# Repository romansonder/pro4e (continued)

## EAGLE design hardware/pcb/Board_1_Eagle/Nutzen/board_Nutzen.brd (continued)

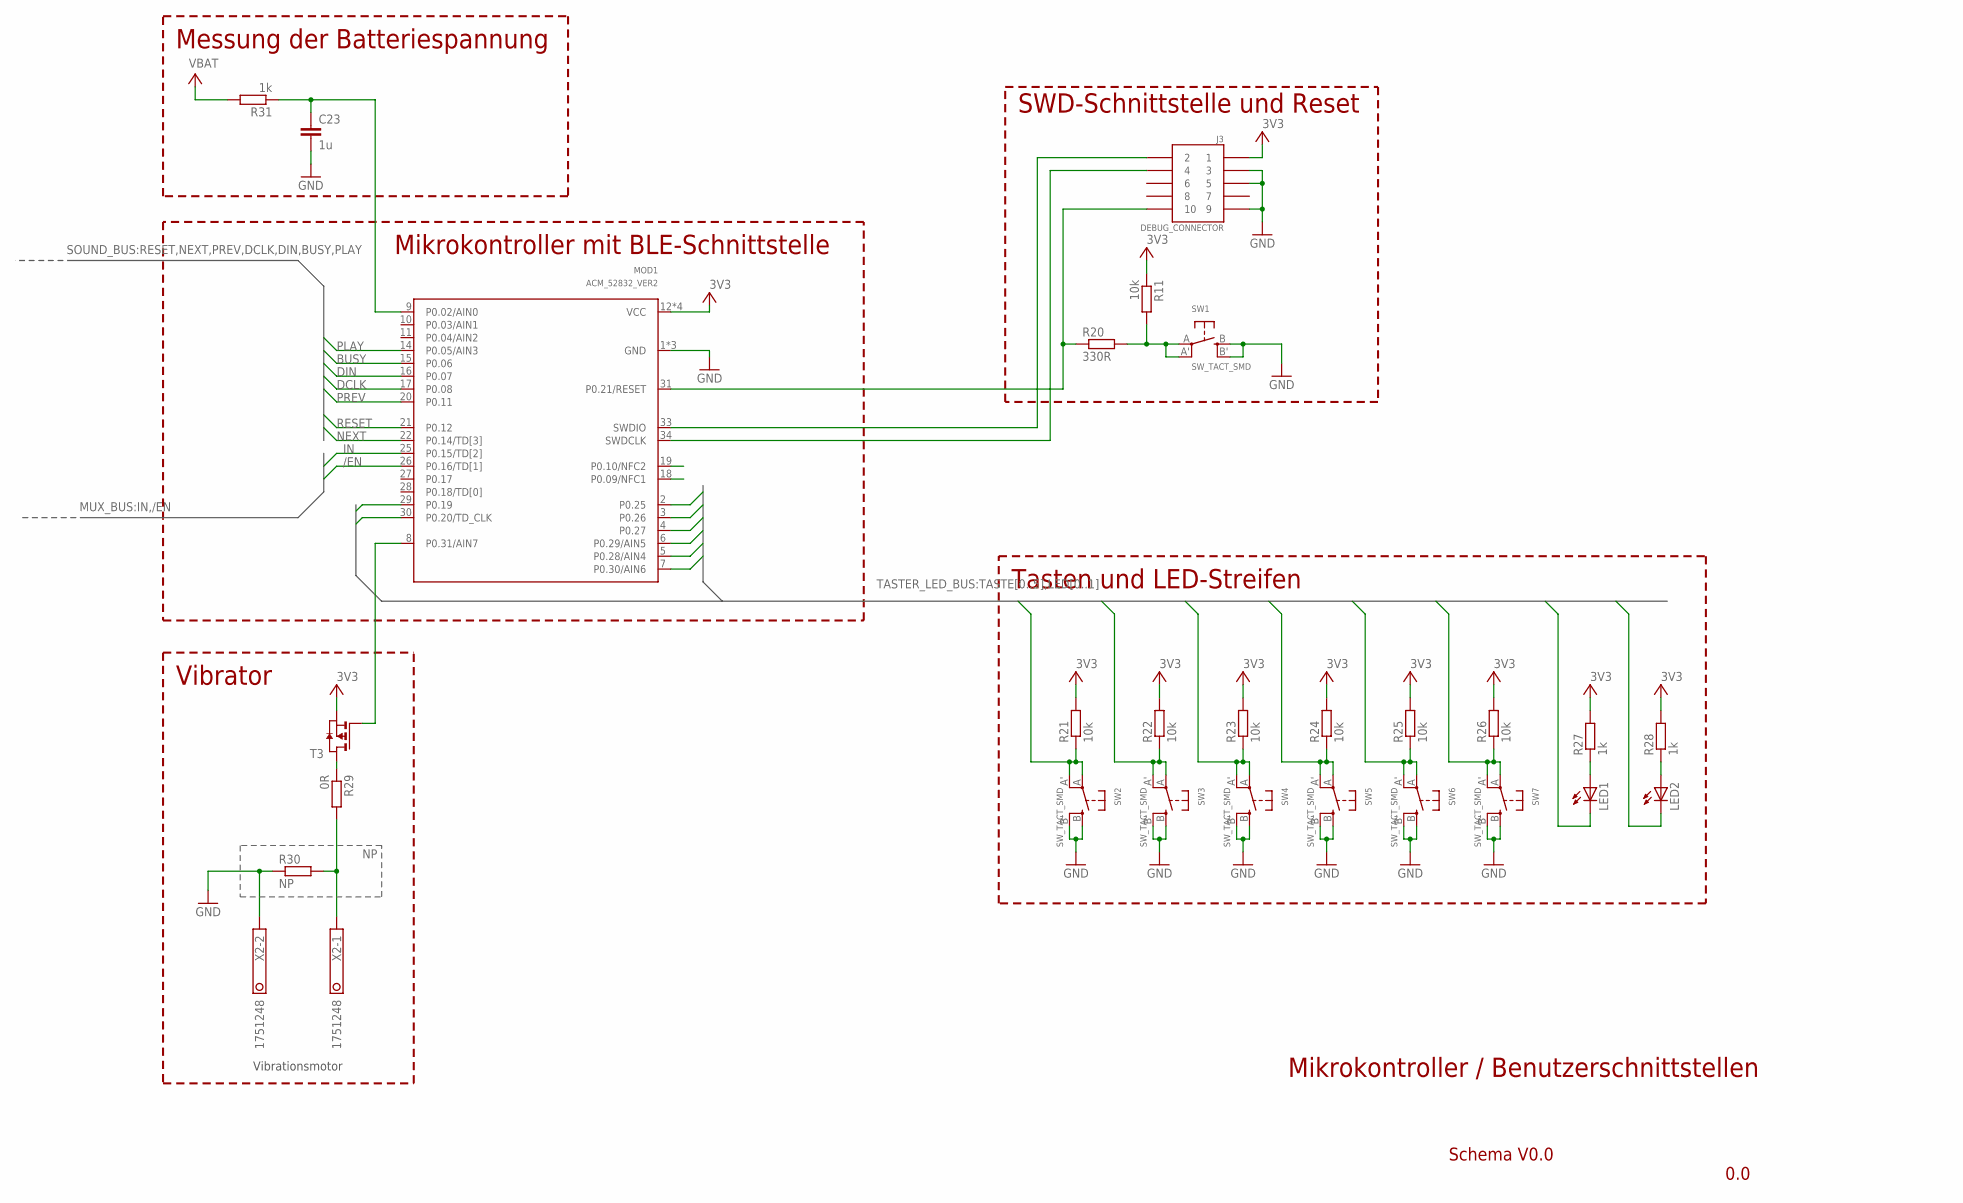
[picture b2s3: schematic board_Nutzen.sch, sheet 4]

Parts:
C23: 1u; C0603
J3: DEBUG_CONNECTOR; HDRV127P5X2-10_N
LED1, LED2: LED_E; LED_1206
MOD1: ACM_52832_VER2; ACONNO_ACM_52832
R11, R21, R22, R23, R24, R25, R26: 10k; R0603
R20: 330R; R0603
R27, R28, R31: 1k; R0603
R29: 0R; R0603
R30: NP; R0603
SW1, SW2, SW3, SW4, SW5, SW6, SW7: SW_TACT_SMD; EVQ-Q2
T3: PMOSSOT23; SOT-23
X2: 1751248

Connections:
+3V3: J3.1, MOD1.12 (VCC), MOD1.23 (VCC), MOD1.24 (VCC), MOD1.32 (VCC), R11.1, R21.2, R22.2, R23.2, R24.2, R25.2, R26.2, R27.2, R28.2, T3.2 (S); also elsewhere on the board
/EN: MOD1.26 (P0.16/TD[1]); also elsewhere on the board
BUSY: MOD1.15 (P0.06); also elsewhere on the board
DCLK: MOD1.17 (P0.08); also elsewhere on the board
DIN: MOD1.16 (P0.07); also elsewhere on the board
GND: C23.2, J3.3, J3.5, J3.9, MOD1.1 (GND), MOD1.13 (GND), MOD1.35 (GND), R30.1, SW1.B (S), SW1.B' (S1), SW2.B (S), SW2.B' (S1), SW3.B (S), SW3.B' (S1), SW4.B (S), SW4.B' (S1), SW5.B (S), SW5.B' (S1), SW6.B (S), SW6.B' (S1), SW7.B (S), SW7.B' (S1), X2.2; also elsewhere on the board
IN: MOD1.25 (P0.15/TD[2]); also elsewhere on the board
LED0: LED1.C, MOD1.29 (P0.19); also elsewhere on the board
LED1: LED2.C, MOD1.30 (P0.20/TD_CLK); also elsewhere on the board
unnamed: R11.2, R20.2, SW1.A, SW1.A' (P1)
unnamed: J3.4, MOD1.34 (SWDCLK)
unnamed: J3.10, MOD1.31 (P0.21/RESET), R20.1
unnamed: J3.2, MOD1.33 (SWDIO)
unnamed: LED1.A, R27.1
unnamed: C23.1, MOD1.9 (P0.02/AIN0), R31.1
unnamed: LED2.A, R28.1
unnamed: R29.2, R30.2, X2.1
unnamed: MOD1.8 (P0.31/AIN7), T3.3 (G)
unnamed: R29.1, T3.1 (D)
NEXT: MOD1.22 (P0.14/TD[3]); also elsewhere on the board
PLAY: MOD1.14 (P0.05/AIN3); also elsewhere on the board
PREV: MOD1.20 (P0.11); also elsewhere on the board
RESET: MOD1.21 (P0.12); also elsewhere on the board
TASTE0: MOD1.7 (P0.30/AIN6), R21.1, SW2.A, SW2.A' (P1); also elsewhere on the board
TASTE1: MOD1.5 (P0.28/AIN4), R22.1, SW3.A, SW3.A' (P1); also elsewhere on the board
TASTE2: MOD1.6 (P0.29/AIN5), R23.1, SW4.A, SW4.A' (P1); also elsewhere on the board
TASTE3: MOD1.4 (P0.27), R24.1, SW5.A, SW5.A' (P1); also elsewhere on the board
TASTE4: MOD1.3 (P0.26), R25.1, SW6.A, SW6.A' (P1); also elsewhere on the board
TASTE5: MOD1.2 (P0.25), R26.1, SW7.A, SW7.A' (P1); also elsewhere on the board
V+: R31.2; also elsewhere on the board

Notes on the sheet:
Vibrationsmotor
Tasten und LED-Streifen
SWD-Schnittstelle und Reset
Vibrator
Messung der Batteriespannung
Mikrokontroller mit BLE-Schnittstelle
Schema V0.0
0.0
Mikrokontroller / Benutzerschnittstellen

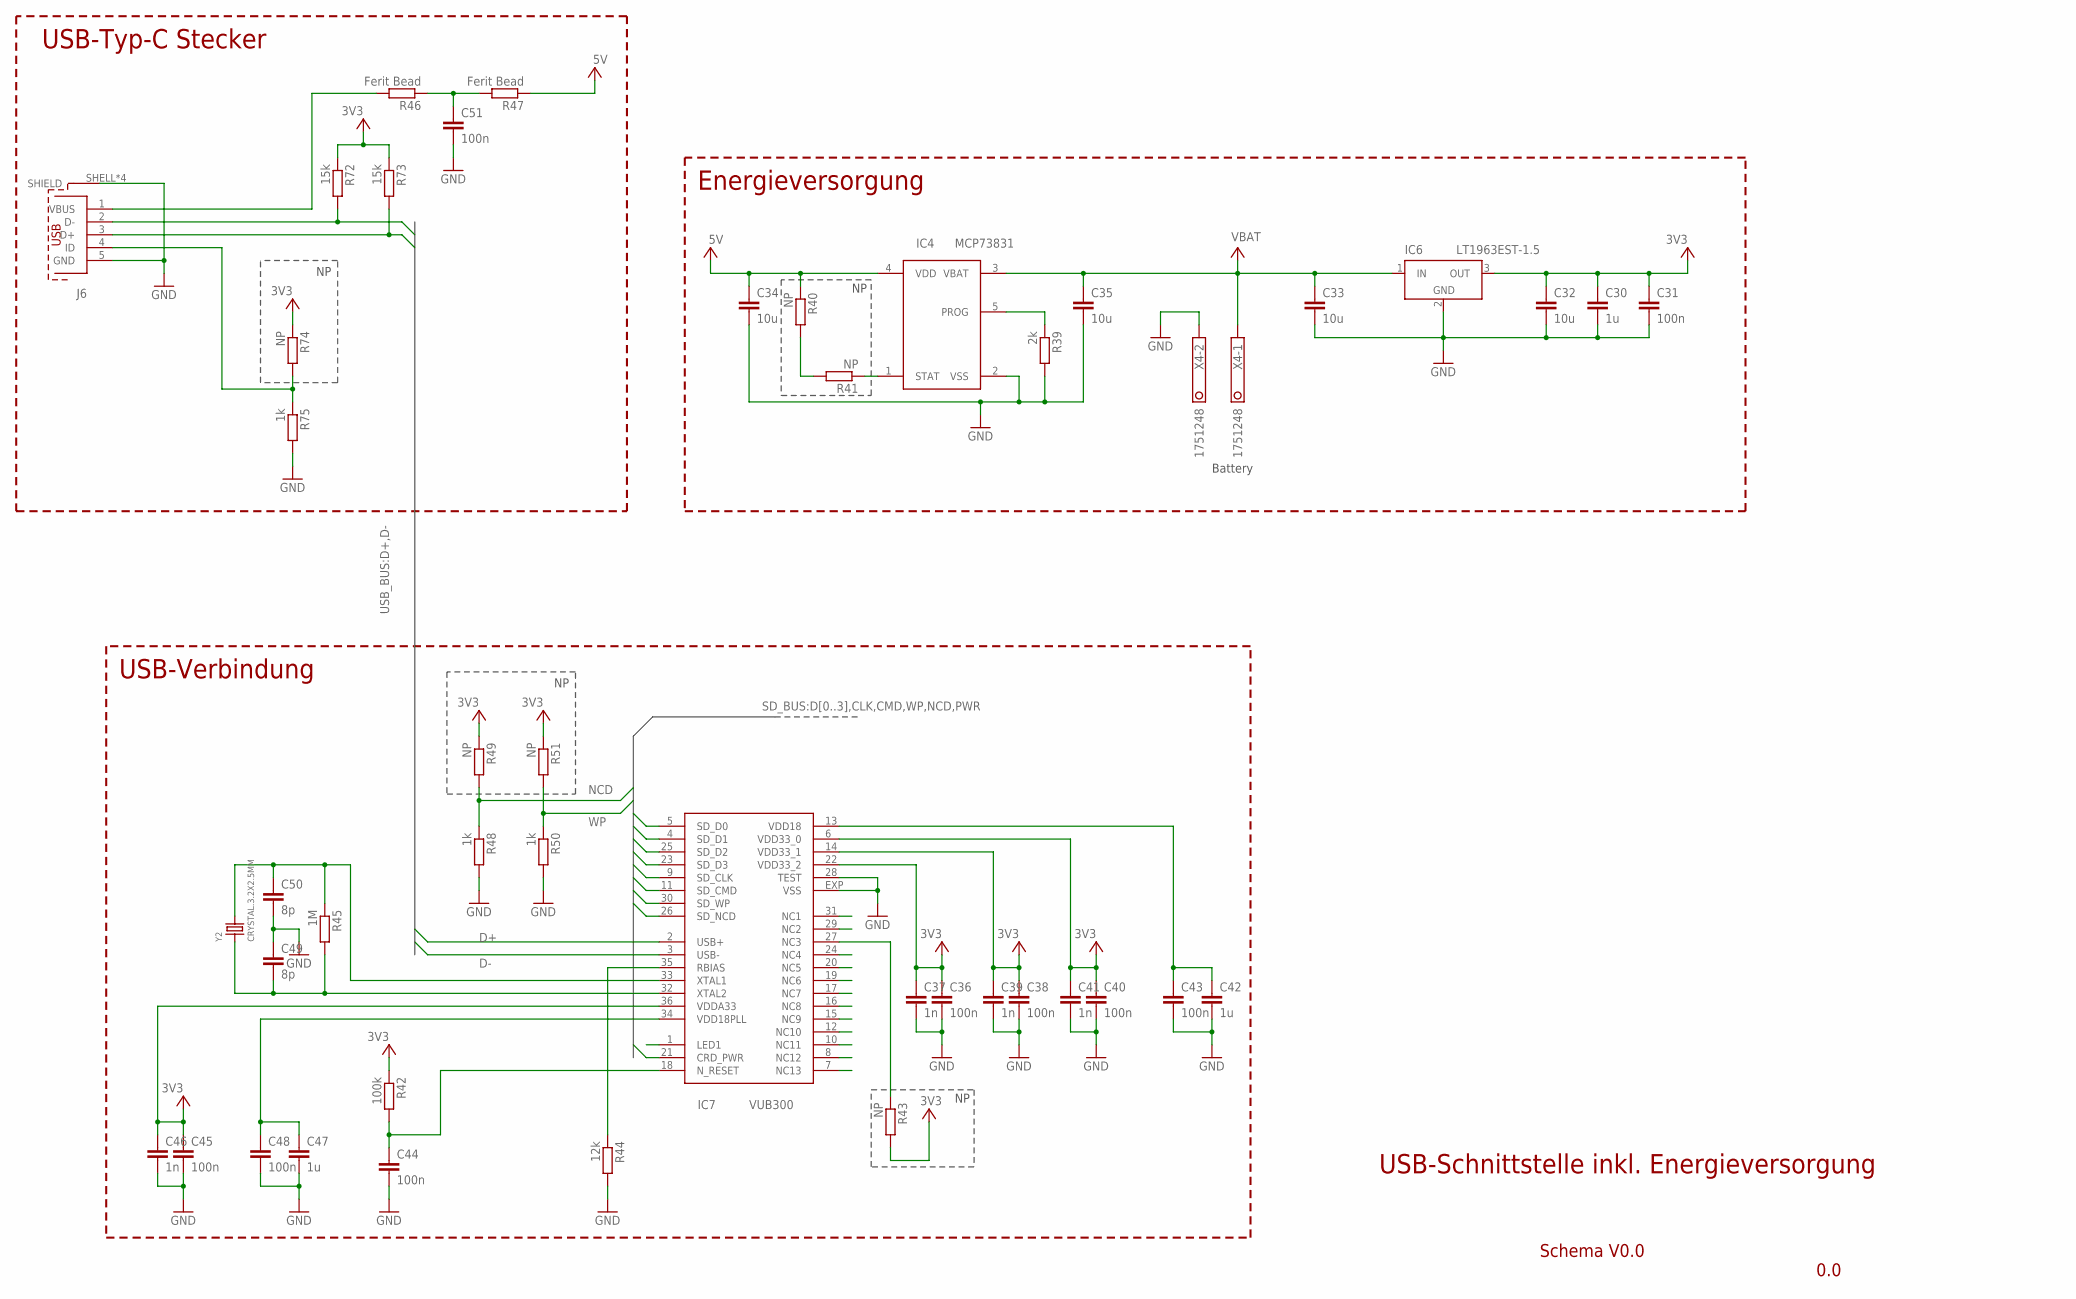
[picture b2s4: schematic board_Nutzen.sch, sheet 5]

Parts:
C30: 1u; C0603
C31, C51: 100n; C0603
C32, C33, C34, C35: 10u; C0805
C36, C38, C40, C43, C44, C45, C48: 100n; C0402
C37, C39, C41, C46: 1n; C0402
C42, C47: 1u; C0402
C49, C50: 8p; C0402
IC4: MCP73831; SOT23-5
IC6: LT1963EST-1.5; SOT223
IC7: VUB300; QFN36-6X6
J6: 629105136821
R39: 2k; R0603
R40, R41, R49, R51, R74: NP; R0603
R42: 100k; R0402
R43: NP; R0402
R44: 12k; R0402
R45: 1M; R0402
R46, R47: Ferit Bead; R0603
R48, R50, R75: 1k; R0603
R72, R73: 15k; R0402
X4: 1751248
Y2: CRYSTAL.3.2X2.5MM; 3.2X2.5MM

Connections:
+3V3: C30.1, C31.1, C32.1, C36.1, C37.1, C38.1, C39.1, C40.1, C41.1, C45.1, C46.1, IC6.3 (OUT), IC7.6 (VDD33_0), IC7.14 (VDD33_1), IC7.22 (VDD33_2), IC7.36 (VDDA33), R42.1, R43.2, R49.1, R51.1, R72.1, R73.1, R74.1; also elsewhere on the board
+5V: C34.1, IC4.4 (VDD), R40.1, R47.1; also elsewhere on the board
CLK: IC7.9 (SD_CLK); also elsewhere on the board
CMD: IC7.11 (SD_CMD); also elsewhere on the board
D0: IC7.5 (SD_D0); also elsewhere on the board
D1: IC7.4 (SD_D1); also elsewhere on the board
D2: IC7.25 (SD_D2); also elsewhere on the board
D3: IC7.23 (SD_D3); also elsewhere on the board
D+: IC7.2 (USB+), J6.3 (D+), R73.2; also elsewhere on the board
D-: IC7.3 (USB-), J6.2 (D-), R72.2; also elsewhere on the board
GND: C30.2, C31.2, C32.2, C33.2, C34.2, C35.2, C36.2, C37.2, C38.2, C39.2, C40.2, C41.2, C42.2, C43.2, C44.2, C45.2, C46.2, C47.2, C48.2, C49.1, C50.2, C51.2, IC4.2 (VSS), IC6.2 (GND), IC6.4 (GND), IC7.28 (TEST), IC7.EXP (VSS), J6.5 (GND), J6.SHELL (SHIELD), J6.SHELL1 (SHIELD), J6.SHELL2 (SHIELD), J6.SHELL3 (SHIELD), R39.2, R44.2, R48.2, R50.2, R75.2, X4.2; also elsewhere on the board
unnamed: IC4.5 (PROG), R39.1
unnamed: R40.2, R41.2
unnamed: IC4.1 (STAT), R41.1
unnamed: C44.1, IC7.18 (N_RESET), R42.2
unnamed: IC7.27 (NC3), R43.1
unnamed: IC7.35 (RBIAS), R44.1
unnamed: C49.2, IC7.32 (XTAL2), R45.2, Y2.1
unnamed: C50.1, IC7.33 (XTAL1), R45.1, Y2.3 (2)
unnamed: J6.1 (VBUS), R46.2
unnamed: C51.1, R46.1, R47.2
unnamed: J6.4 (ID), R74.2, R75.1
NCD: IC7.26 (SD_NCD), R48.1, R49.2; also elsewhere on the board
PWR: IC7.21 (CRD_PWR); also elsewhere on the board
V+: C33.1, C35.1, IC4.3 (VBAT), IC6.1 (IN), X4.1; also elsewhere on the board
VDD18: C42.1, C43.1, IC7.13 (VDD18); also elsewhere on the board
VDD18PLL: C47.1, C48.1, IC7.34 (VDD18PLL); also elsewhere on the board
WP: IC7.30 (SD_WP), R50.1, R51.2; also elsewhere on the board

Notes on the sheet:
Battery
USB-Typ-C Stecker
Energieversorgung
USB-Verbindung
Schema V0.0
0.0
USB-Schnittstelle inkl. Energieversorgung

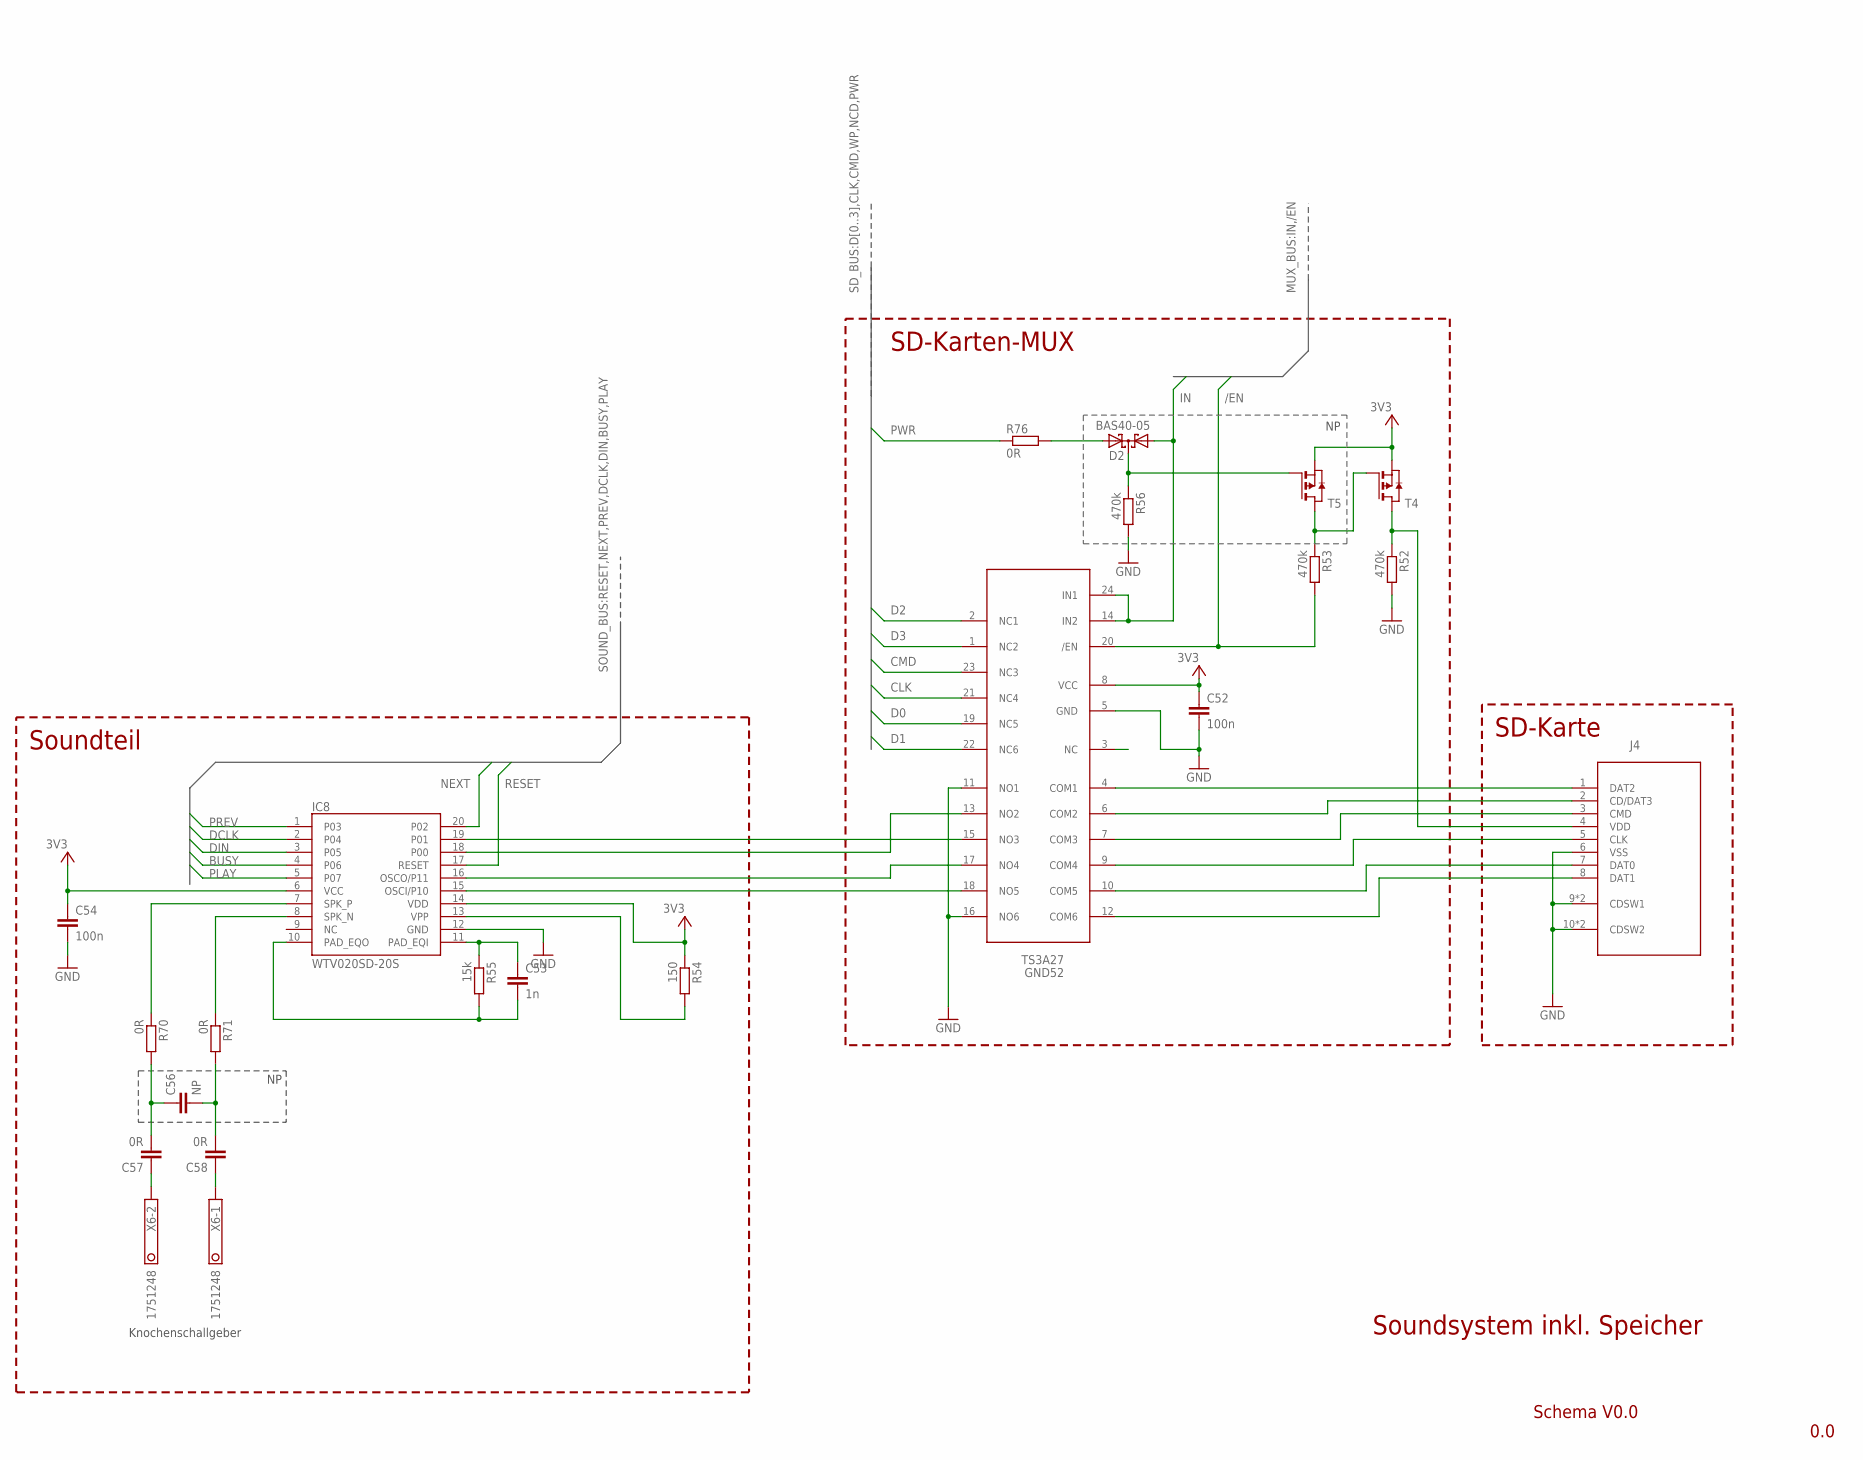
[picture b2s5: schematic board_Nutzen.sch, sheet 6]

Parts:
C52, C54: 100n; C0603
C53: 1n; C0603
C56: NP; C0603
C57, C58: 0R; C0603
D2: BAS40-05; SOT23
GND52: TS3A27; TSSOP24
IC8: WTV020SD-20S; SSOP_20
J4: 693071010811
R52, R53, R56: 470k; R0603
R54: 150; R0603
R55: 15k; R0603
R70, R71: 0R; R0603
R76: 0R; MINI_MELF-0102W
T4, T5: PMOSSOT23; SOT-23
X6: 1751248

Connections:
+3V3: C52.1, C54.1, GND52.8 (VCC), IC8.6 (VCC), IC8.14 (VDD), R54.1, T4.2 (S), T5.2 (S); also elsewhere on the board
/EN: GND52.20 (/EN), R53.2; also elsewhere on the board
BUSY: IC8.4 (P06); also elsewhere on the board
CLK: GND52.21 (NC4); also elsewhere on the board
CMD: GND52.23 (NC3); also elsewhere on the board
D0: GND52.19 (NC5); also elsewhere on the board
D1: GND52.22 (NC6); also elsewhere on the board
D2: GND52.2 (NC1); also elsewhere on the board
D3: GND52.1 (NC2); also elsewhere on the board
DCLK: IC8.2 (P04); also elsewhere on the board
DIN: IC8.3 (P05); also elsewhere on the board
GND: C52.2, C54.2, GND52.5 (GND), GND52.11 (NO1), GND52.16 (NO6), IC8.12 (GND), J4.6 (VSS), J4.9 (CDSW1), J4.9-1 (CDSW1), J4.10 (CDSW2), J4.10-1 (CDSW2), R52.2, R56.2; also elsewhere on the board
IN: D2.1 (A1), GND52.14 (IN2), GND52.24 (IN1); also elsewhere on the board
unnamed: GND52.9 (COM4), J4.5 (CLK)
unnamed: IC8.13 (VPP), R54.2
unnamed: C53.1, IC8.11 (PAD_EQI), R55.1
unnamed: GND52.17 (NO4), IC8.16 (OSCO/P11)
unnamed: GND52.18 (NO5), IC8.15 (OSCI/P10)
unnamed: GND52.6 (COM2), J4.2 (CD/DAT3)
unnamed: GND52.4 (COM1), J4.1 (DAT2)
unnamed: GND52.12 (COM6), J4.8 (DAT1)
unnamed: R53.1, T4.3 (G), T5.1 (D)
unnamed: D2.3 (C), R56.1, T5.3 (G)
unnamed: C57.1, X6.2
unnamed: C58.1, X6.1
unnamed: C56.2, C58.2, R71.2
unnamed: C56.1, C57.2, R70.2
unnamed: D2.2 (A2), R76.2
unnamed: GND52.15 (NO3), IC8.19 (P01)
NCD2: J4.4 (VDD), R52.1, T4.1 (D)
NEXT: IC8.20 (P02); also elsewhere on the board
PLAY: IC8.5 (P07); also elsewhere on the board
PREV: IC8.1 (P03); also elsewhere on the board
PWM1: C53.2, IC8.10 (PAD_EQO), R55.2
PWR: R76.1; also elsewhere on the board
RESET: IC8.17 (RESET); also elsewhere on the board
SDCS1: GND52.13 (NO2), IC8.18 (P00)
SDDI1: GND52.7 (COM3), J4.3 (CMD)
SDDO1: GND52.10 (COM5), J4.7 (DAT0)
SPK+1: IC8.7 (SPK_P), R70.1
SPK-1: IC8.8 (SPK_N), R71.1

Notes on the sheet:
SD-Karten-MUX
SD-Karte
Soundteil
Schema V0.0
0.0
Soundsystem inkl. Speicher
Knochenschallgeber

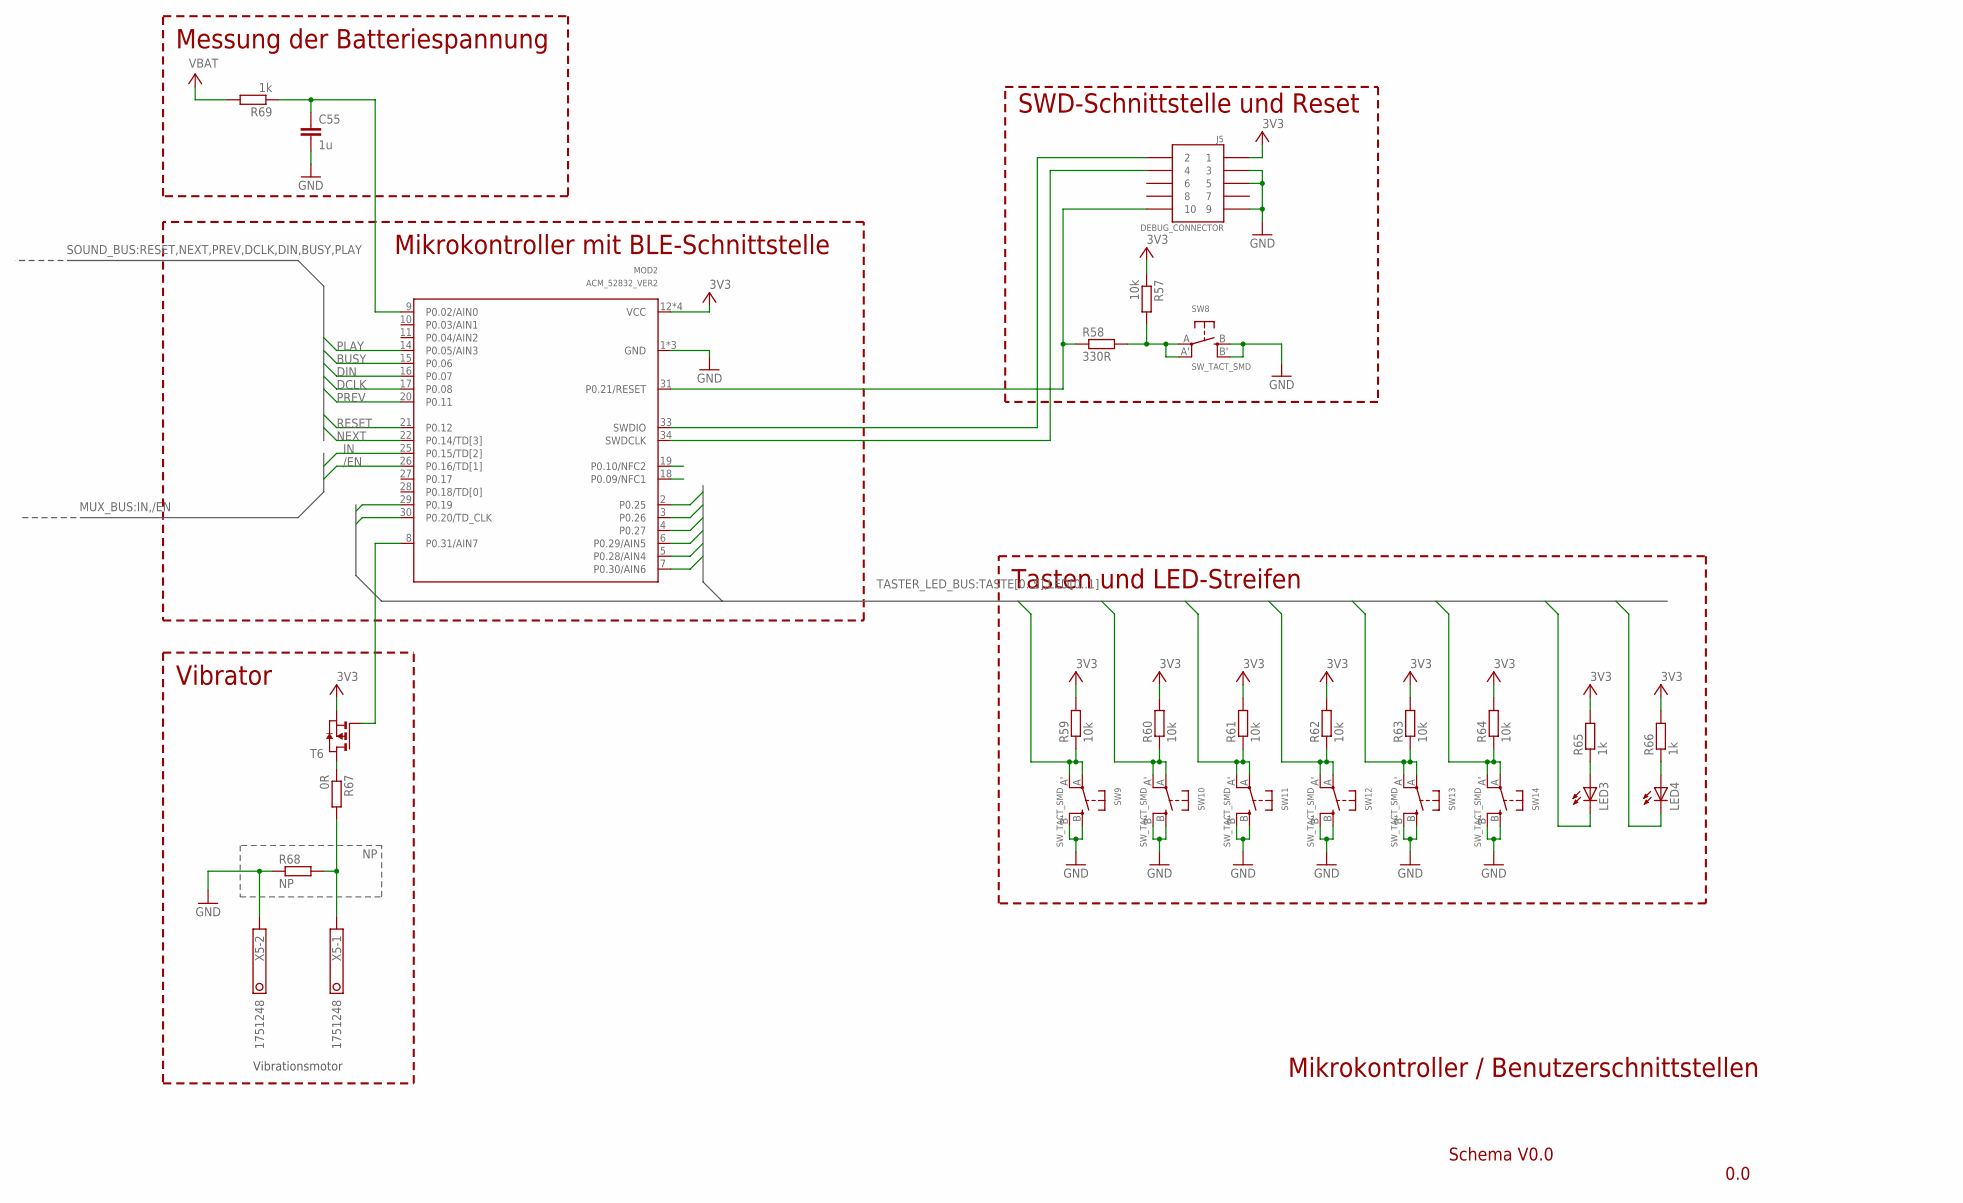
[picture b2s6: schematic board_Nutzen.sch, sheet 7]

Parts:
C55: 1u; C0603
J5: DEBUG_CONNECTOR; HDRV127P5X2-10_N
LED3, LED4: LED_E; LED_1206
MOD2: ACM_52832_VER2; ACONNO_ACM_52832
R57, R59, R60, R61, R62, R63, R64: 10k; R0603
R58: 330R; R0603
R65, R66, R69: 1k; R0603
R67: 0R; R0603
R68: NP; R0603
SW8, SW9, SW10, SW11, SW12, SW13, SW14: SW_TACT_SMD; EVQ-Q2
T6: PMOSSOT23; SOT-23
X5: 1751248

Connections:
+3V3: J5.1, MOD2.12 (VCC), MOD2.23 (VCC), MOD2.24 (VCC), MOD2.32 (VCC), R57.1, R59.2, R60.2, R61.2, R62.2, R63.2, R64.2, R65.2, R66.2, T6.2 (S); also elsewhere on the board
/EN: MOD2.26 (P0.16/TD[1]); also elsewhere on the board
BUSY: MOD2.15 (P0.06); also elsewhere on the board
DCLK: MOD2.17 (P0.08); also elsewhere on the board
DIN: MOD2.16 (P0.07); also elsewhere on the board
GND: C55.2, J5.3, J5.5, J5.9, MOD2.1 (GND), MOD2.13 (GND), MOD2.35 (GND), R68.1, SW8.B (S), SW8.B' (S1), SW9.B (S), SW9.B' (S1), SW10.B (S), SW10.B' (S1), SW11.B (S), SW11.B' (S1), SW12.B (S), SW12.B' (S1), SW13.B (S), SW13.B' (S1), SW14.B (S), SW14.B' (S1), X5.2; also elsewhere on the board
IN: MOD2.25 (P0.15/TD[2]); also elsewhere on the board
LED0: LED3.C, MOD2.29 (P0.19); also elsewhere on the board
LED1: LED4.C, MOD2.30 (P0.20/TD_CLK); also elsewhere on the board
unnamed: R57.2, R58.2, SW8.A, SW8.A' (P1)
unnamed: J5.10, MOD2.31 (P0.21/RESET), R58.1
unnamed: J5.2, MOD2.33 (SWDIO)
unnamed: J5.4, MOD2.34 (SWDCLK)
unnamed: LED3.A, R65.1
unnamed: LED4.A, R66.1
unnamed: MOD2.8 (P0.31/AIN7), T6.3 (G)
unnamed: R67.2, R68.2, X5.1
unnamed: R67.1, T6.1 (D)
unnamed: C55.1, MOD2.9 (P0.02/AIN0), R69.1
NEXT: MOD2.22 (P0.14/TD[3]); also elsewhere on the board
PLAY: MOD2.14 (P0.05/AIN3); also elsewhere on the board
PREV: MOD2.20 (P0.11); also elsewhere on the board
RESET: MOD2.21 (P0.12); also elsewhere on the board
TASTE0: MOD2.7 (P0.30/AIN6), R59.1, SW9.A, SW9.A' (P1); also elsewhere on the board
TASTE1: MOD2.5 (P0.28/AIN4), R60.1, SW10.A, SW10.A' (P1); also elsewhere on the board
TASTE2: MOD2.6 (P0.29/AIN5), R61.1, SW11.A, SW11.A' (P1); also elsewhere on the board
TASTE3: MOD2.4 (P0.27), R62.1, SW12.A, SW12.A' (P1); also elsewhere on the board
TASTE4: MOD2.3 (P0.26), R63.1, SW13.A, SW13.A' (P1); also elsewhere on the board
TASTE5: MOD2.2 (P0.25), R64.1, SW14.A, SW14.A' (P1); also elsewhere on the board
V+: R69.2; also elsewhere on the board

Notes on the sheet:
Vibrationsmotor
Tasten und LED-Streifen
SWD-Schnittstelle und Reset
Vibrator
Messung der Batteriespannung
Mikrokontroller mit BLE-Schnittstelle
Schema V0.0
0.0
Mikrokontroller / Benutzerschnittstellen

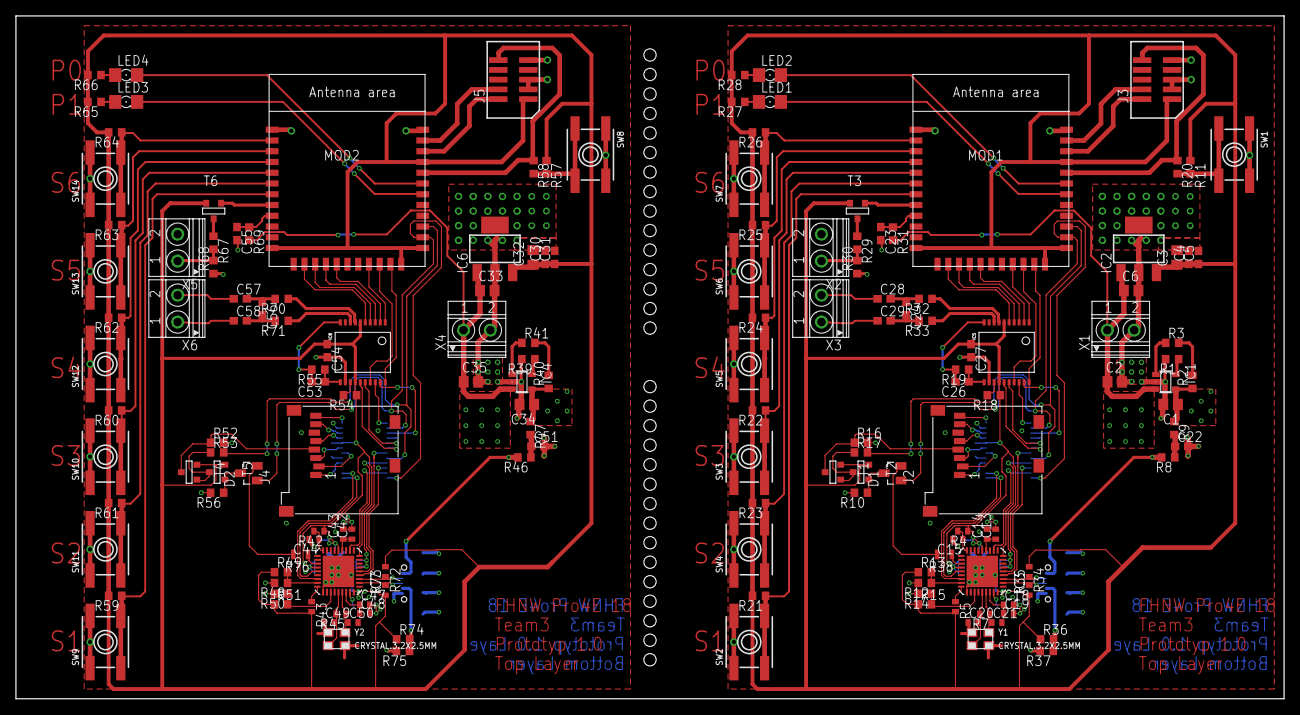
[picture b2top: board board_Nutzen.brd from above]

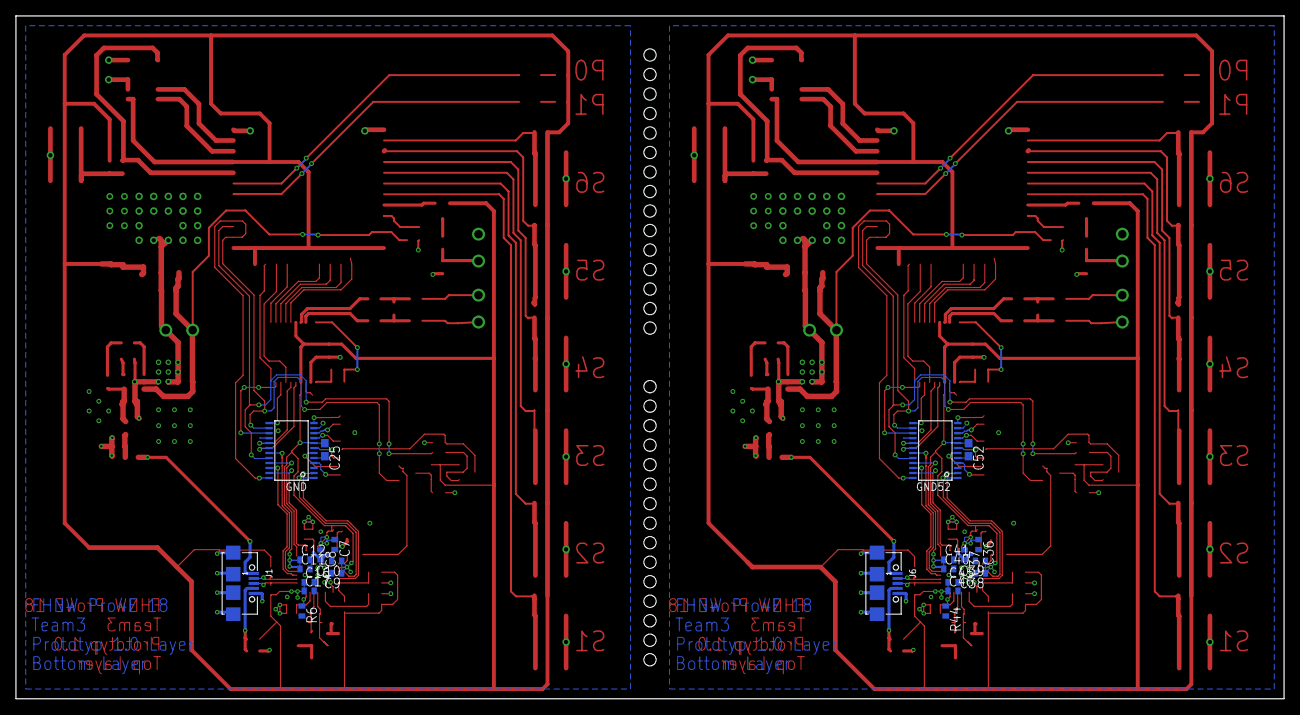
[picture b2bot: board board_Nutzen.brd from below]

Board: 2 copper layers, 165.1 x 88.9 mm, 186 parts (24 on the bottom side), 122 nets.

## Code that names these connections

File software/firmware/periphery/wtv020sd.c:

/* lizenz */

/* wtv020sd Audiointerface */

#include <stdbool.h>
#include <stdint.h>

#include "nrf_delay.h"
#include "nrf_gpio.h"
#include "dojo.h"


#include "wtv020sd.h"

/******************************************************************************/
static void wtv020sd_send(uint16_t command);

/******************************************************************************/
/* edit IO-Ports as you need them */
static const uint32_t data_pin = AUDIO_DIN_PIN;
static const uint32_t reset_pin = AUDIO_RESET_PIN;
static const uint32_t clk_pin = AUDIO_DCLK_PIN;
static const uint32_t busy_pin = AUDIO_BUSY_PIN;

/* edit unsused Pins on Dojoboard */
static const uint32_t play_pin = AUDIO_PLAY_PIN;
static const uint32_t prev_pin = AUDIO_PREV_PIN;
static const uint32_t next_pin = AUDIO_NEXT_PIN;


static uint16_t current_vol = VOL_MAX;

/******************************************************************************/
/* set-up inputs and outputs for communication to audio interface */
extern void wtv020sd_init(void){
	/* define outputs */
	nrf_gpio_cfg_output(data_pin);
	nrf_gpio_cfg_output(clk_pin);

	nrf_gpio_cfg(reset_pin, NRF_GPIO_PIN_DIR_OUTPUT, NRF_GPIO_PIN_INPUT_DISCONNECT, NRF_GPIO_PIN_NOPULL, NRF_GPIO_PIN_S0D1, NRF_GPIO_PIN_NOSENSE);

	/* set pins to no data */
	nrf_gpio_pin_set(data_pin);
	nrf_gpio_pin_set(clk_pin);

	nrf_gpio_pin_set(reset_pin);

	/* define inputs */
	nrf_gpio_cfg_input(busy_pin, NRF_GPIO_PIN_NOPULL);
	nrf_gpio_cfg_input(play_pin, NRF_GPIO_PIN_NOPULL);
	nrf_gpio_cfg_input(prev_pin, NRF_GPIO_PIN_NOPULL);
	nrf_gpio_cfg_input(next_pin, NRF_GPIO_PIN_NOPULL);


	/* define start volume */
	wtv020sd_send(current_vol);
	wtv020sd_reset();
}

extern void wtv020sd_play_pause(void){
	wtv020sd_send(PLAY_PAUSE);
}

extern void wtv020sd_stop(void){
	wtv020sd_send(STOP);
}

extern void wtv020sd_inc_vol(void){
	if(current_vol < VOL_MAX){
		current_vol = current_vol + 1;
		wtv020sd_send(current_vol);
	}
}

extern void wtv020sd_dec_vol(void){
	if(current_vol > VOL_MIN){
		current_vol = current_vol - 1;
		wtv020sd_send(current_vol);
	}
}

extern void wtv020sd_reset(void){
	nrf_gpio_pin_set(clk_pin);

	nrf_gpio_pin_set(reset_pin);

	/* trigger reset pin */
	nrf_gpio_pin_clear(reset_pin);
	nrf_delay_ms(100);
	nrf_gpio_pin_set(reset_pin);

	nrf_delay_ms(500);
}

extern void wtv020sd_play_audio(uint16_t audio_name){
	wtv020sd_send(audio_name);
}

extern uint8_t wtv020sd_status(void){
	return 1;
}

/******************************************************************************/
static void wtv020sd_send(uint16_t command){
	/* clock init */
	nrf_gpio_pin_clear(clk_pin);
	nrf_delay_ms(2);

	for(int i = 15; i > -1; i--){
		/* first half low clock pulse */
		nrf_gpio_pin_clear(clk_pin);
		nrf_delay_us(100);

		uint16_t mask = 0x0001;
		if(mask & (~mask | (command >> i))){
			nrf_gpio_pin_set(data_pin);
		}else{
			nrf_gpio_pin_clear(data_pin);
		}

		/* second half low clock pulse */
		nrf_delay_us(100);

		/* full high clock pulse */
		nrf_gpio_pin_set(clk_pin);
		nrf_delay_us(200);

	}

	nrf_gpio_pin_set(data_pin);
	nrf_gpio_pin_set(clk_pin);

	/* wait for busy activity from interface*/
	nrf_delay_ms(20);
}

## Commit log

2018-02-21 Initial commit.
2018-02-21 Structuring commit
2018-02-22 README changed
2018-02-22 README changes
2018-02-25 changes in Presentation
2018-02-26 Changes in gitignor list
2018-02-26 gitingorlist added
2018-02-27 changes in product_specification
2018-02-28 blubb
2018-03-01 organisatorische pflichteheft zum grösste teil gschriebe
2018-03-06 Neue Bilder und Einleitung,Organigramm und Budget geschrieben
2018-03-06 Rechtschreibung und ergänzungen
2018-03-06 Added first version of dojo testsoftware.
2018-03-06 Layout verbesserung
2018-03-06 Added second version of dojo testsoftware.
2018-03-06 Added third version of dojo testsoftware.
2018-03-12 finetuning
2018-03-13 kei ahnig was ich gmacht ha
2018-03-13 Introduced new GUITypes.
2018-03-13 Lesefürung hinzugefügt
2018-03-13 Organigramm updated
2018-03-14 exitet text of tecnical product spec.
2018-03-15 Added logic for table and first testdata
2018-03-15 Implemented first logic for outputparameter area.
2018-03-15 some more text
2018-03-17 Implemented JOptionDialog for creation of new objects and added first testdata.
2018-03-18 Implemented new column settings and style.
2018-03-18 rechtschreibung
2018-03-18 Name falsch :D
2018-03-18 korrektur
2018-03-18 final version :-)
2018-03-18 Fix Fertig :-)
2018-03-20 New java executable
2018-03-20 Test 01
2018-03-20 status Function added
2018-03-20 audio driver update
2018-03-20 Piuss Testet
    Hoi zäme bin gad am teste
2018-03-20 Für Pius
2018-03-20 Test retour
    Huhu
2018-03-20 test
2018-03-20 Implemented delete function and created new jar executable.
2018-03-20 First part of layout done and added design rules.
2018-03-20 Implemented correct file extension handling and created new executable jar.
2018-03-21 Made some cleanup
2018-03-21 VUB300 gelayoutet
2018-03-22 Layout
2018-03-24 Final Version ;-)
2018-03-24 Implemented menubar and aboutus screen.
2018-03-25 Changed file extension to fix about us screen and some cleanup.
2018-03-27 lsökj
2018-03-28 Layout angepasst. Verstärker hinzugefügt
2018-03-29 new project plan
2018-04-13 sadf
2018-04-23 Added first version of serial communication
2018-04-23 Implemented museum data transmitting.
2018-04-23 Implemented data transmitting
2018-04-23 Hardware Pius
    Fachbricht gschribe über Energieversorgig
2018-04-23 ergänzungen
2018-04-23 korrekturen
2018-04-23 beginn einleitung
2018-04-24 Added help descriptions
2018-04-24 Disposition
    Neus Dokument fürt Disposition
2018-04-24 Implemented extracting of dojo information
2018-04-24 Disposition
    Disposition fertiggestellt
2018-04-24 Revert "Merge branch 'master' of https://github.com/romansonder/pro4e"
    This reverts commit b431f28ab4204237c71f1241374e504c8ce5763b, reversing
    changes made to 1fa79df36be0a64204c9bb9dab450b398c5ac2e6.
2018-04-24 readme erweitert
2018-04-24 laden und entlade kapitel geschrieben
2018-04-24 Bider eingefügt
2018-04-24 Einleitung
    Einleitung in Dispo übernommen
2018-04-24 Implemented first version of JavaBle protocol.
2018-04-24 Implemented second version of JavaBle protocol.
2018-04-24 ladeleistungs kurve
2018-04-24 Korrekturen Hardwareteil
    Am Emerson sis zügs duregläse
2018-04-24 Implemented port combobox and added new runnable jar.
2018-04-25 Improved error handling.
2018-04-25 Abstract und Wirkungsgrad berechnung
2018-04-25 Grundlagen
    Grundlagen Aufbau Dojo
2018-04-25 Made some clean up
2018-04-25 Implemented multithreading for data transmitting.
2018-04-25 Grundlagen
    1 Teil fertig
2018-04-25 Clean up
2018-04-25 Compiled new runnable jar.
2018-04-25 Removed abstract from headline.
2018-04-26 Implemented first version of usermanual.
2018-04-26 Added missing files.
2018-04-26 Plots hinzugefügt und korrekturen
2018-04-26 Extended usermanual
2018-04-26 Einleitung und Tabellenverzeichnis/Abbildungsverzeichnis
2018-04-26 öldsaf
2018-04-26 Harware
    Ich will Github zerstören!!
2018-04-26 Hardware änderige
    Jess
2018-04-26 reparatur
2018-04-26 Einleitung und Verzeichnis
2018-04-26 Renaming of folder
2018-05-08 Improved einnleitung
2018-05-08 Removed duplicated folders.
2018-05-08 laborbericht update
2018-05-08 Energieversorgig fertig
    Mal luege öb das dräcks Github wider abstürzt.
2018-05-09 software update
2018-05-10 Added new version of disposition from Dominik Hiltbrunner.
2018-05-10 Added new version of abstract and einleitung to fachbericht.
2018-05-10 Some corrections.
2018-05-10 Kleine Korektur
2018-05-10 Changed language handling and added new test data.
2018-05-10 Implemented prevention for creating more than one audio file for the same language and ID.
2018-05-11 Zusatz Einleitung
2018-05-11 Update Einletung Fachbericht
2018-05-14 Implemented sorting function for JTable and improved creation dialog for new museum objects.
2018-05-14 Removed save button from command panel to menubar.
2018-05-15 Some small improvements for adding dialog of new museum objects.
2018-05-15 Extended user manual with new informations.
2018-05-15 Just some renaming stuff.
2018-05-16 dsaf
2018-05-16 Merged revision(s) 180 from : dsaf
    ........
2018-05-16 Added separate file for definitions.
2018-05-16 Small corrections
2018-05-16 Changed description of file formats.
2018-05-17 Started with Grundlagen and deleted old not stuff.
2018-05-20 First subsection of arbeitsgrundlagen done.
2018-05-20 Second subsection of arbeitsgrundlagen done.
2018-05-20 Finished chapter 1 of documention.
2018-05-20 Second chapter done.
2018-05-20 Cleanup of my stuff.
2018-05-22 Added appendix content.
2018-05-22 some stuff
2018-05-24 Fix for data transmitting on linux systems.
2018-05-24 Cleanup
2018-05-24 Added new logo.
2018-05-24 Corrected Logo
2018-05-29 Fachbricht überarbeitig gemäss Github
    Han wider mal Lust s'Github z'zerstöre
2018-05-30 Made calculcation of n.
2018-05-30 Just some renamings.
2018-06-01 Grundlage überarbeitet
    Gruess Pius
2018-06-01 Änderungen im Softwareteil der Doku
2018-06-02 Grossbuchstaben klein gemacht bei Bilderbezeichnung.
2018-06-03 afds
2018-06-03 sfda
2018-06-03 fdsa
2018-06-03 huhui
2018-06-05 PMA-Bricht hinzuegfüegt
    Github gang kabutt looooos:
    Gruess Pius
2018-06-05 PMA Vorgabe ueglade.
    Anhand vo dem chamer de PMA Bricht schribe.
2018-06-05 fehler korrigiert
    Juhuu has wider gschafft.
    Nieder mitem Github.
2018-06-05 Software stuff
2018-06-05 schnappi
2018-06-05 Final version of usermanual.
2018-06-06 div. Aenderige unter anderem PMA und die eint Zeichnig
    Judihuii
2018-06-07 huhu
2018-06-07 Improved exception handling.
2018-06-07 adsf
2018-06-07 ölkj
2018-06-07 lfdsajk
2018-06-07 Final version of Java Testsoftware.
2018-06-07 Added lorem ipsum version of factsheet.
2018-06-07 Changed to german version
2018-06-07 Prepared for pma docs.
2018-06-07 Implemented my part for pma report.
2018-06-08 Implemented timout of 5 seconds for not responding dojo.
2018-06-08 Added first version of executive summary.
2018-06-08 Just some label renaming on gui.
2018-06-08 Implemented license.
2018-06-08 New .jar with license
2018-06-08 Implemented topView in Model to have parent for JFileChoosers.
2018-06-09 Implemented always closing of port.
2018-06-09 Korrektur bis Kapitel 3
2018-06-09 Chlini Änderige Grundlage
    Gruess
2018-06-09 Created first version of fact-sheet.
2018-06-09 Ileitig Überarbeitet
    Anhand de Dubach irne Sache überarbeitet und in Duden prüeft.
2018-06-09 PMA fertiggstellt Ileitig erwitered und Schlusswort gschribe
2018-06-09 safdoo
2018-06-10 PM-Bericht Zitatfehler behoben
2018-06-10 new folder for english related stuff
2018-06-10 Wiederherstellen der Korekturen
2018-06-11 Correction of PMA
2018-06-11 abstract and management summary
2018-06-11 Latex endversion
2018-06-12 ENDVERSION
2018-06-12 last corrections
2018-06-13 Simtool
2018-06-14 Added adapted simulation.
2018-06-14 Simulation
2018-06-15 Online correction with duden.
